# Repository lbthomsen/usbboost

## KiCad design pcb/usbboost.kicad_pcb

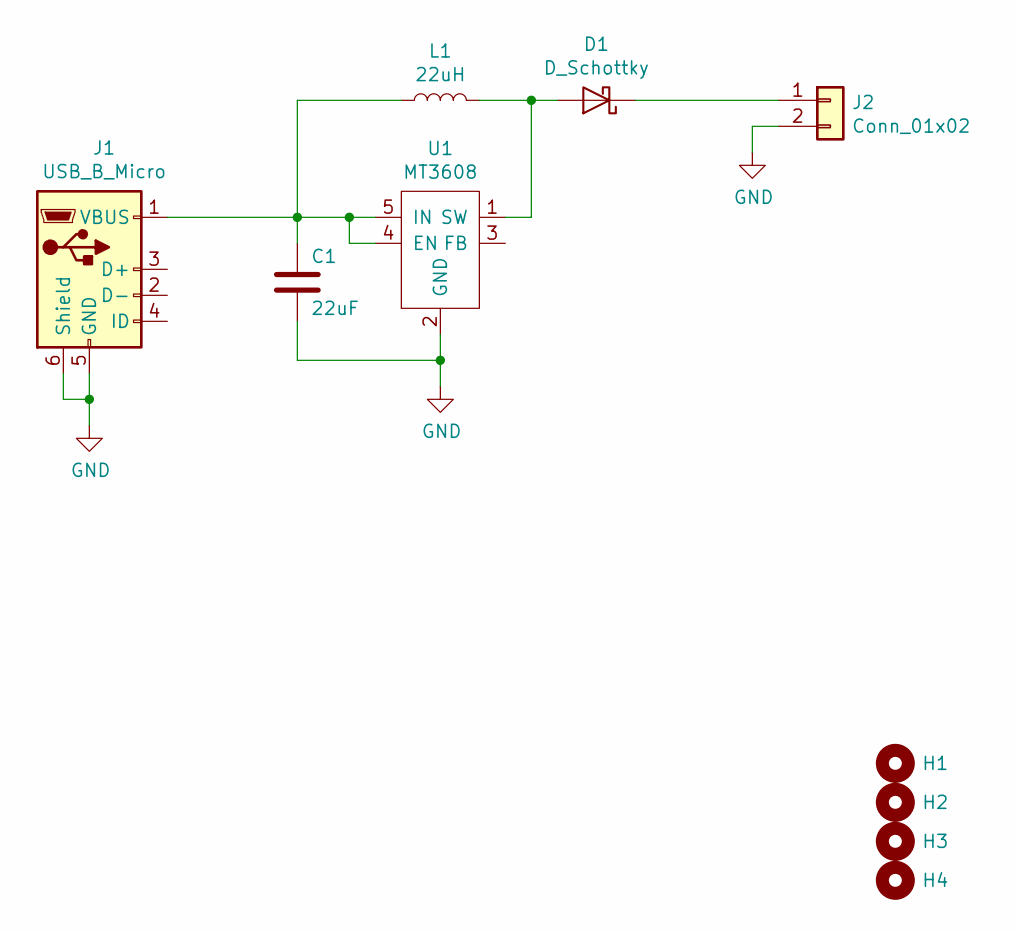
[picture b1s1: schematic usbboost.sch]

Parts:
C1: 22uF; C_0603_1608Metric
D1: D_Schottky; D_0603_1608Metric_Castellated
H1, H2, H3, H4: MountingHole_2.2mm_M2
J1: USB_B_Micro; USB_Micro-B_Molex-105017-0001
J2: Conn_01x02; PinHeader_1x02_P2.54mm_Vertical
L1: 22uH; L_1210_3225Metric
U1: MT3608; SOT-23-6

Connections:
GND: C1.2, J1.5 (GND), J1.6 (Shield), J2.2, U1.2 (GND)
unnamed: C1.1, J1.1 (VBUS), L1.1, U1.4 (EN), U1.5 (IN)
unnamed: D1.1 (K), J2.1
unnamed: D1.2 (A), L1.2, U1.1 (SW)

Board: 2 copper layers, 10 parts (0 on the bottom side), 4 nets, no tracks yet.

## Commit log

2019-08-12 Started
